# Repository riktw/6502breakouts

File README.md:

Some boards to hook up a logic analyzer to a 6502 and 6510.

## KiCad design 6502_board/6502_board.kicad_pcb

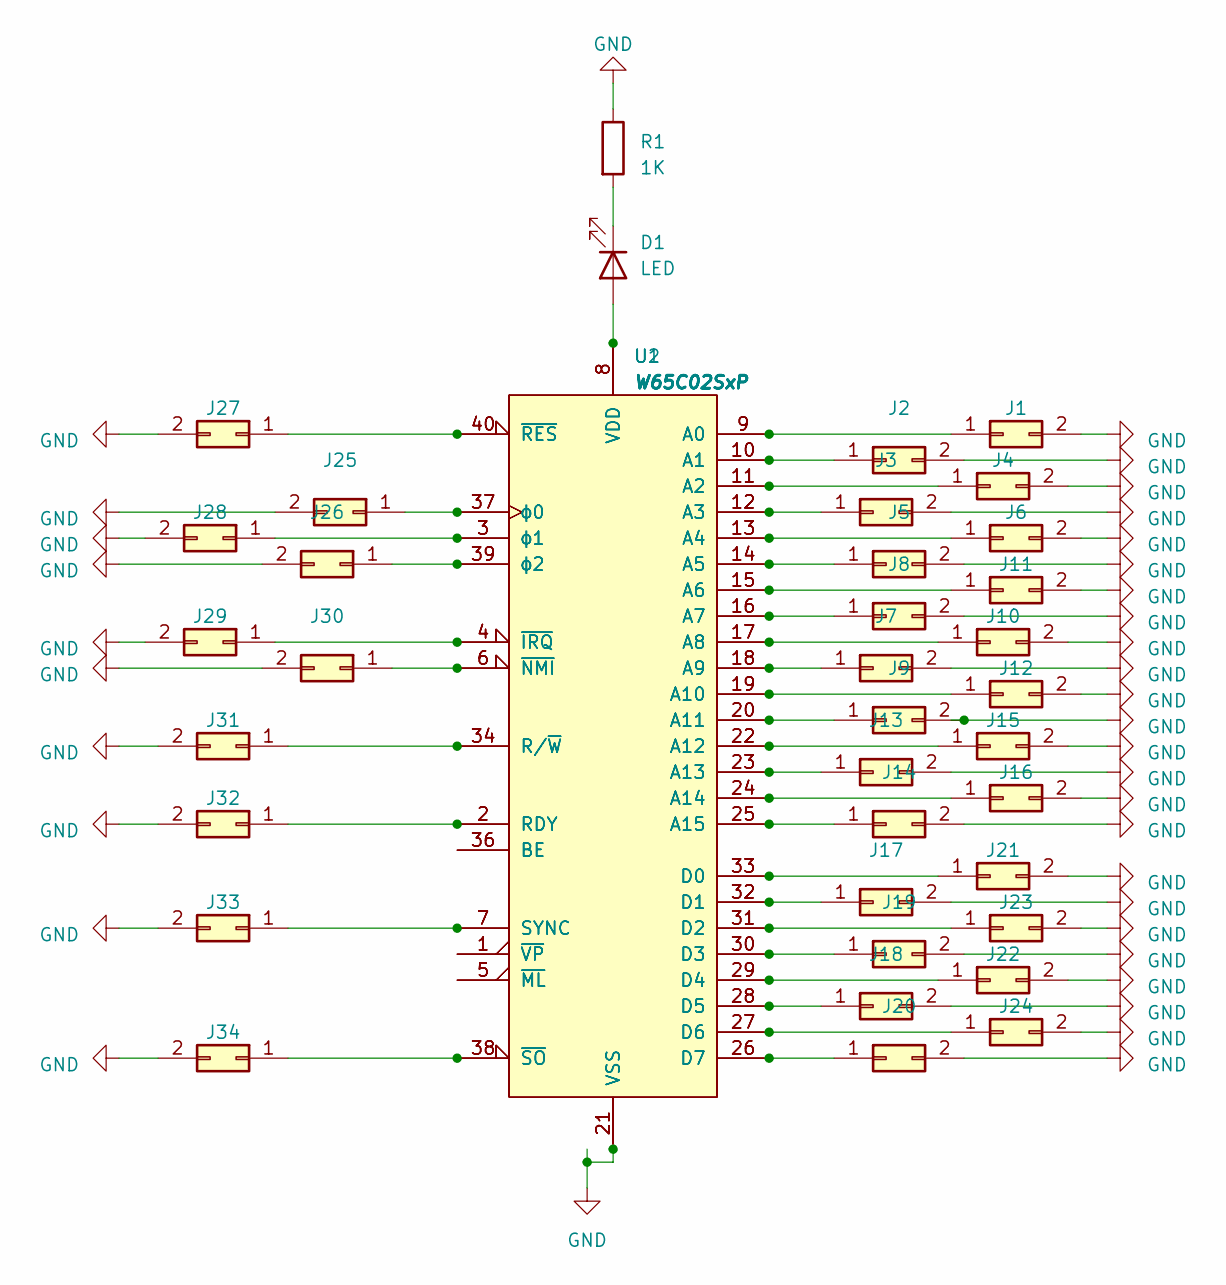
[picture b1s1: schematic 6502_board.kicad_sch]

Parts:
D1: LED; LED_D3.0mm
J1, J2, J3, J4, J5, J6, J7, J8, J9, J10, J11, J12, J13, J14, J15, J16, J17, J18, J19, J20, J21, J22, J23, J24, J25, J26, J27, J28, J29, J30, J31, J32, J33, J34: Conn_02x01; PinHeader_2x01_P2.54mm_Vertical
R1: 1K; R_Axial_DIN0207_L6.3mm_D2.5mm_P10.16mm_Horizontal
U1, U2: W65C02SxP; DIP-40_W15.24mm

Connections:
GND: J1.2, J2.2, J3.2, J4.2, J5.2, J6.2, J7.2, J8.2, J9.2, J10.2, J11.2, J12.2, J13.2, J14.2, J15.2, J16.2, J17.2, J18.2, J19.2, J20.2, J21.2, J22.2, J23.2, J24.2, J25.2, J26.2, J27.2, J28.2, J29.2, J30.2, J31.2, J32.2, J33.2, J34.2, R1.1, U1.21 (VSS), U2.21 (VSS)
unnamed: D1.2 (A), U1.8 (VDD), U2.8 (VDD)
unnamed: D1.1 (K), R1.2
unnamed: J1.1, U1.9 (A0), U2.9 (A0)
unnamed: J2.1, U1.10 (A1), U2.10 (A1)
unnamed: J3.1, U1.12 (A3), U2.12 (A3)
unnamed: J4.1, U1.11 (A2), U2.11 (A2)
unnamed: J5.1, U1.14 (A5), U2.14 (A5)
unnamed: J6.1, U1.13 (A4), U2.13 (A4)
unnamed: J7.1, U1.18 (A9), U2.18 (A9)
unnamed: J8.1, U1.16 (A7), U2.16 (A7)
unnamed: J9.1, U1.20 (A11), U2.20 (A11)
unnamed: J10.1, U1.17 (A8), U2.17 (A8)
unnamed: J11.1, U1.15 (A6), U2.15 (A6)
unnamed: J12.1, U1.19 (A10), U2.19 (A10)
unnamed: J13.1, U1.23 (A13), U2.23 (A13)
unnamed: J14.1, U1.25 (A15), U2.25 (A15)
unnamed: J15.1, U1.22 (A12), U2.22 (A12)
unnamed: J16.1, U1.24 (A14), U2.24 (A14)
unnamed: J17.1, U1.32 (D1), U2.32 (D1)
unnamed: J18.1, U1.28 (D5), U2.28 (D5)
unnamed: J19.1, U1.30 (D3), U2.30 (D3)
unnamed: J20.1, U1.26 (D7), U2.26 (D7)
unnamed: J21.1, U1.33 (D0), U2.33 (D0)
unnamed: J22.1, U1.29 (D4), U2.29 (D4)
unnamed: J23.1, U1.31 (D2), U2.31 (D2)
unnamed: J24.1, U1.27 (D6), U2.27 (D6)
unnamed: J25.1, U1.37 (ϕ0), U2.37 (ϕ0)
unnamed: J26.1, U1.39 (ϕ2), U2.39 (ϕ2)
unnamed: J27.1, U1.40 (~RES), U2.40 (~RES)
unnamed: J28.1, U1.3 (ϕ1), U2.3 (ϕ1)
unnamed: J29.1, U1.4 (~IRQ), U2.4 (~IRQ)
unnamed: J30.1, U1.6 (~NMI), U2.6 (~NMI)
unnamed: J31.1, U1.34 (R/~W), U2.34 (R/~W)
unnamed: J32.1, U1.2 (RDY), U2.2 (RDY)
unnamed: J33.1, U1.7 (SYNC), U2.7 (SYNC)
unnamed: J34.1, U1.38 (~SO), U2.38 (~SO)
unnamed: U1.36 (BE), U2.36 (BE)
unnamed: U1.5 (~ML), U2.5 (~ML)
unnamed: U1.1 (~VP), U2.1 (~VP)

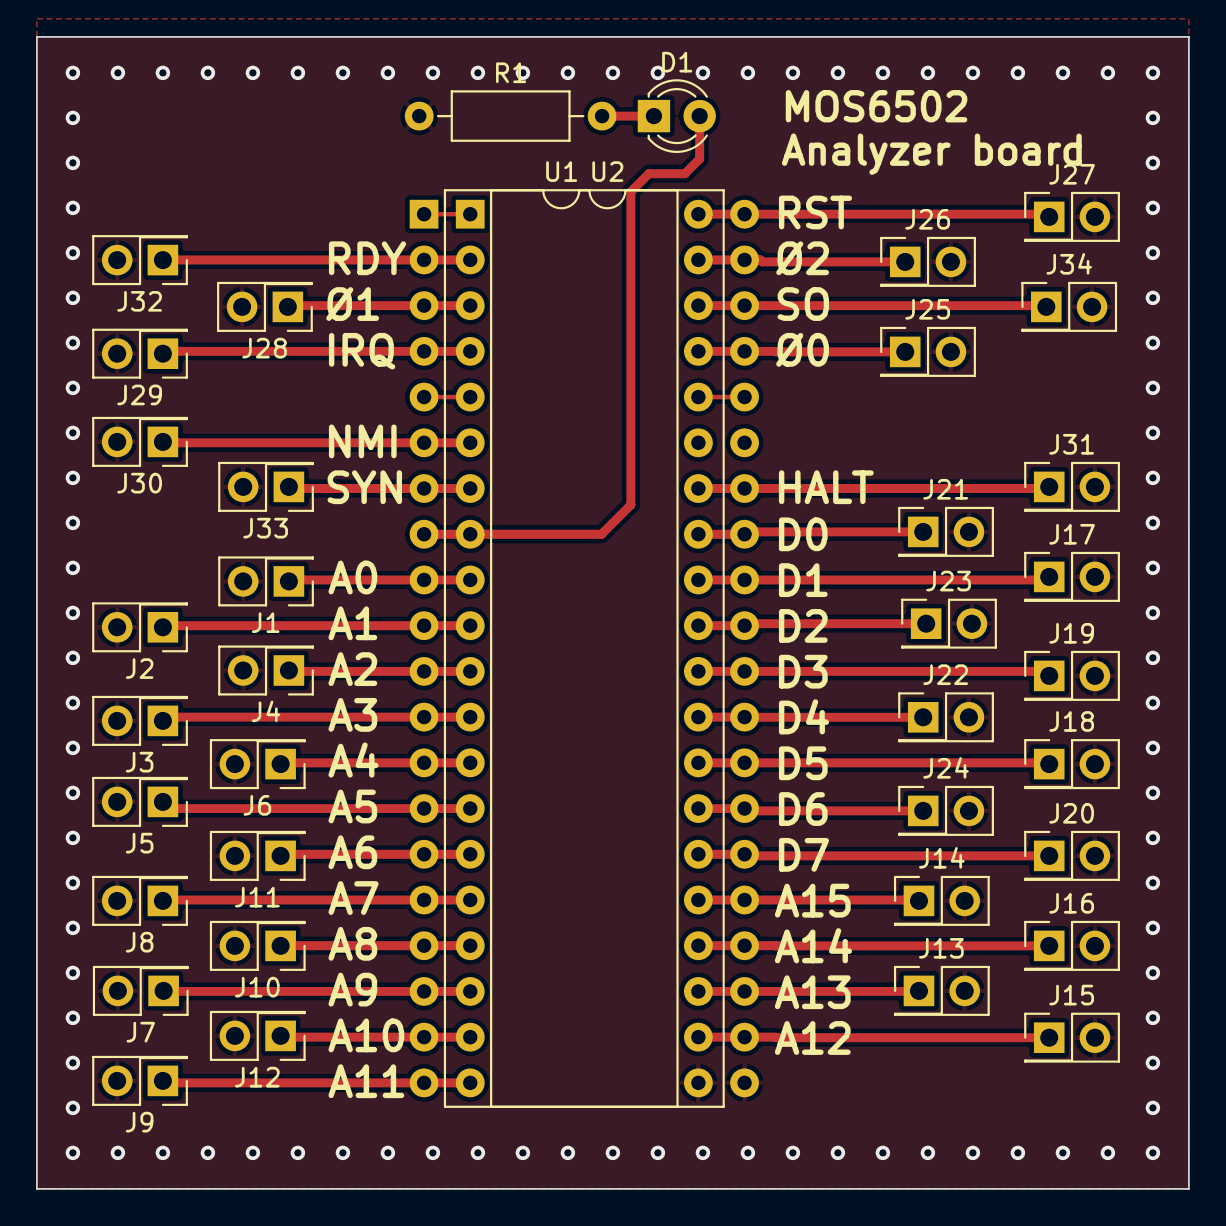
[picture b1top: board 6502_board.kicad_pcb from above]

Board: 2 copper layers, 64.0 x 64.0 mm, 38 parts (0 on the bottom side), 40 nets.

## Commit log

2023-06-14 Initial checkin
